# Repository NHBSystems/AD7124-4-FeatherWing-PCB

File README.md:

# AD7124-4 24bit Analog Sensor FeatherWing Design Files

This is a new Feather compatible board for reading precision analog sensors like load cells, thermocouples, and strain gauges. It uses the AD7124-4, a 4 channel, 24 bit, differential ADC (Can also be configured as 7 single ended channels). Like the [6 Channel 24 bit Featherwing](https://github.com/NHBSystems/6Ch-24bit-FeatherWing-PCB) this board is designed for lower power, monitoring type applications, however it can also be configured for significantly higher sampling rates than the AD7794. The board also includes a low pass anti-aliasing filter on the inputs, a 5th input pin for a shield wire connection, and software enabled excitation voltage without using an additional pin.

**Specifications**

- RMS noise down to 23 nV at 9.4 SPS
- Low power operation with 3 conversion power modes
- Power-down current of 5 μA maximum (AD7124 chip)
- Low noise, programmable gain instrumentation amplifier (1 to 128)
- Band gap reference with 10 ppm/°C drift typical
- Simultaneous 50 Hz/60 Hz rejection at 25 SPS
- Update rate: Up to 19200 sps (per datasheet for single channel)
- 4 differential analog inputs, (or 7 single ended)
- Independent configuration of each channel
- Low pass anti-aliasing filter on inputs
- 5 pin connections with excitation, ground, and shield for each channel
- Shield can be tied to chassis or to ground (trace jumper on bottom)
- On board 2.5v LDO controlled in software without needing additional pin
- Software enabled bias voltage on all channels (for reading thermocouples)

This board can be purchased assembled here: [24 bit Analog Sensor FeatherWing](https://www.tindie.com/products/24680/)

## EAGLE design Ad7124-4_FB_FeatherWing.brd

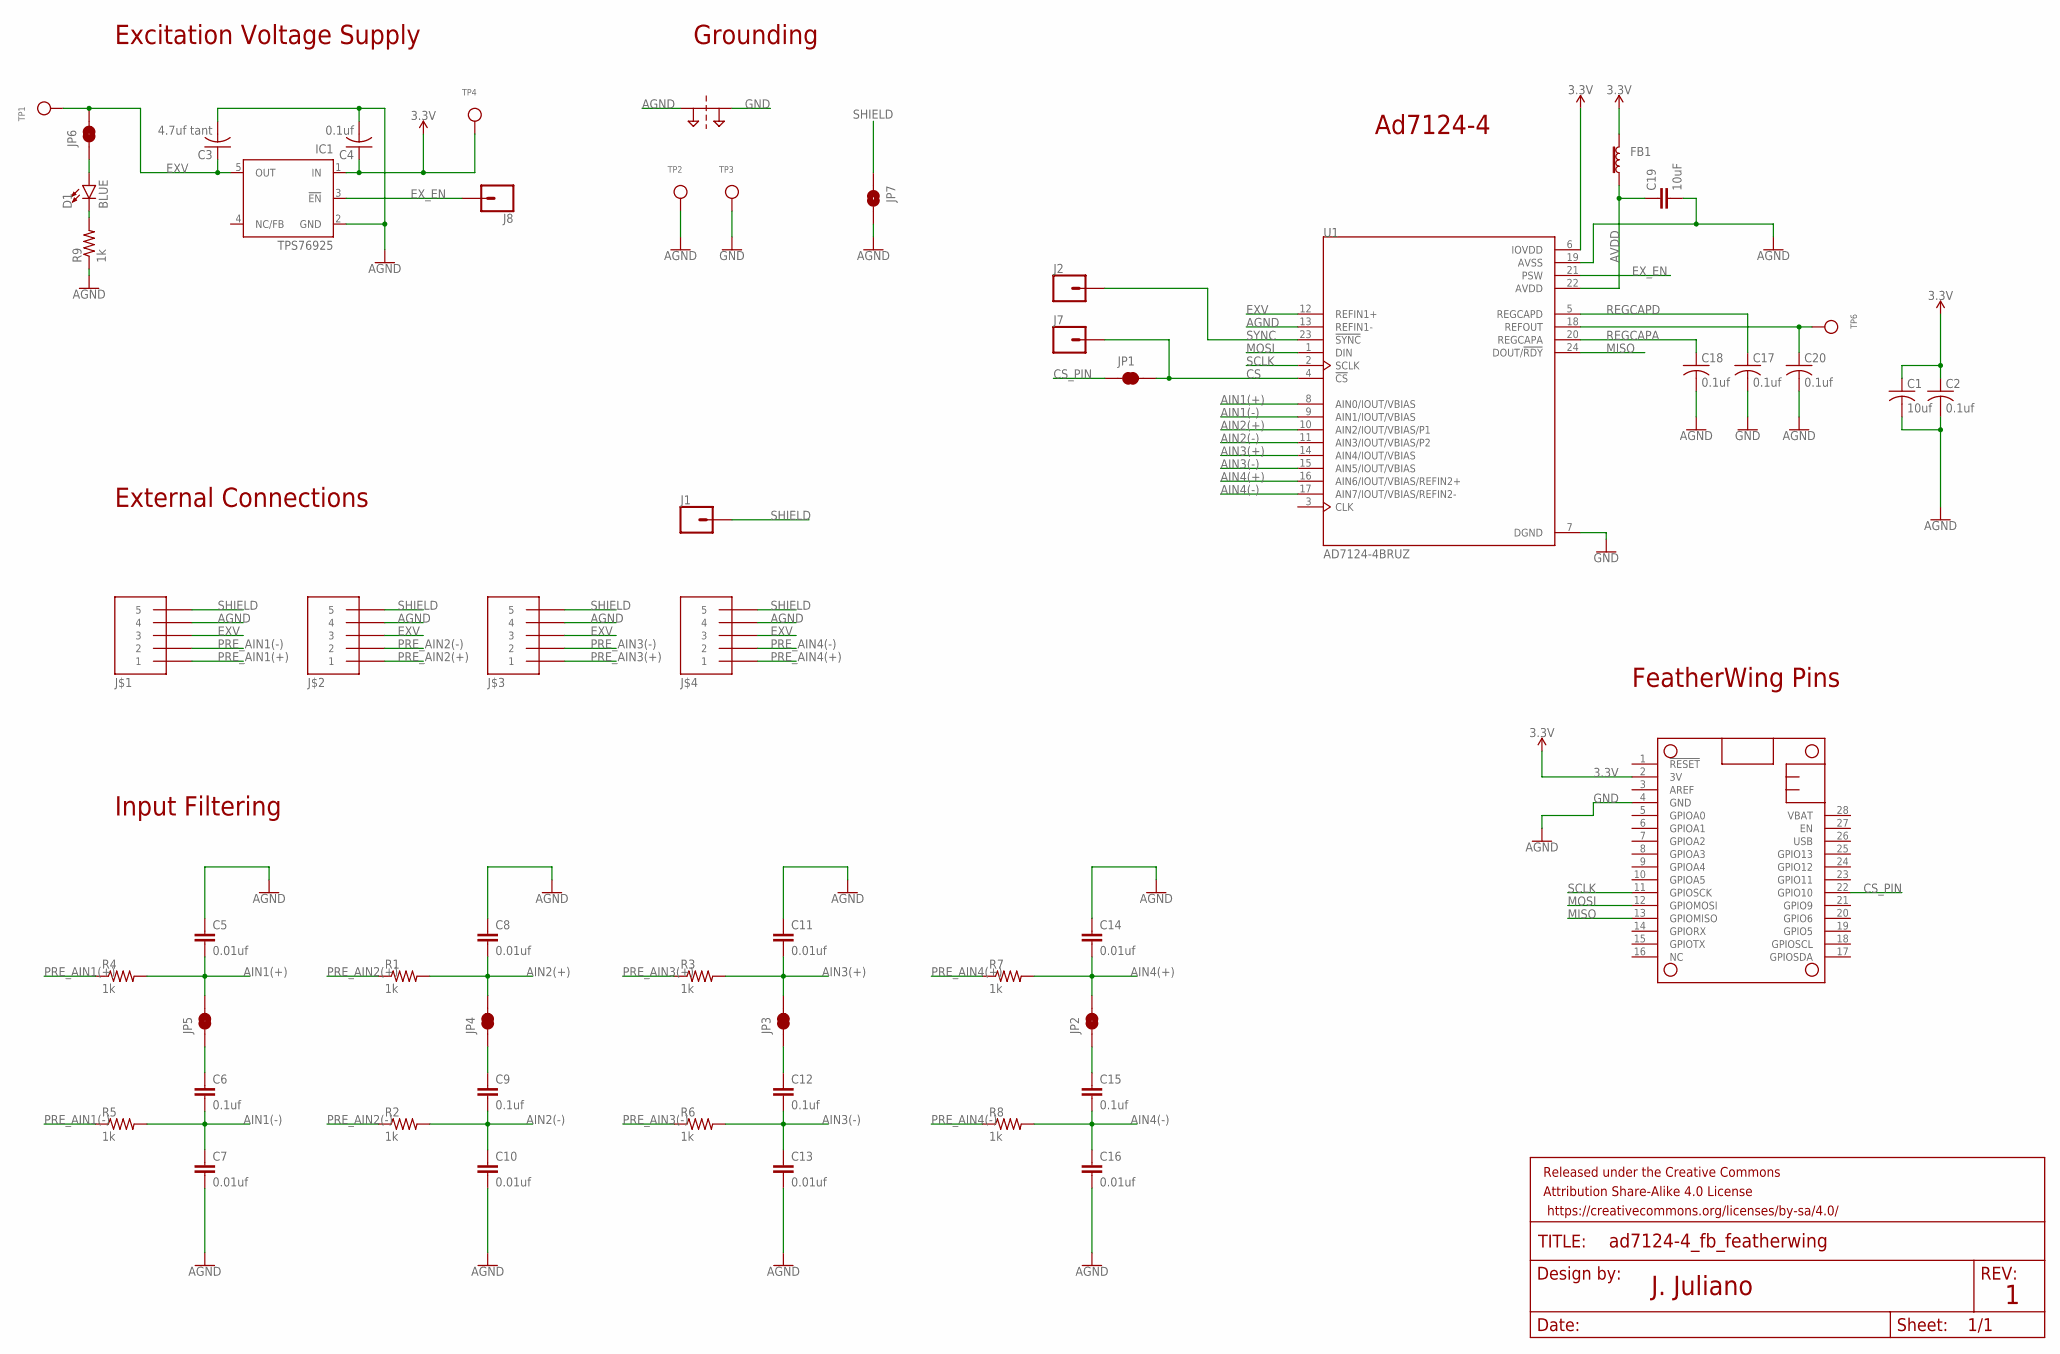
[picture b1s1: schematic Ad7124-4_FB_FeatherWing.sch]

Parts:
C1: 10uf; C0603
C2, C4, C6, C9, C12, C15, C17, C18, C20: 0.1uf; C0603
C3: 4.7uf tant; C0603
C5, C7, C8, C10, C11, C13, C14, C16: 0.01uf; C0603
C19: 10uF; 0603
D1: BLUE; LED-0603
FB1: FERRITE_BEAD-0603; 0603
FRAME2: FRAME-LETTER; CREATIVE_COMMONS
IC1: TPS76925; SOT23-DBV
J1, J2, J7, J8: CONN_01PTH_NO_SILK_YES_STOP; 1X01_NO_SILK
J$1, J$2, J$3, J$4: CON_PTSM_SOCKET-5-PTH-VERT
JP1, JP2, JP3, JP4, JP5, JP6: JUMPER-SMT_2_NC_TRACE_NO-SILK; SMT-JUMPER_2_NC_TRACE_NO-SILK
JP7: JUMPER-SMT_2_NO_NO-SILK; SMT-JUMPER_2_NO_NO-SILK
MS1: FEATHERWING_NODIM; FEATHERWING_DIM
R1, R2, R3, R4, R5, R6, R7, R8, R9: 1k; R0603
SUPPLY6: 2PT_GND_TIE
TP1, TP2, TP3, TP4, TP6: TESTPOINTROUND1MM; TESTPOINT_ROUND_1MM
U1: AD7124-4BRUZ; SOP65P640X120-24N

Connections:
3.3V: C1.1, C2.1, C4.1, FB1.2, IC1.1 (IN), MS1.2 (3V), TP4.P$1, U1.6 (IOVDD)
AGND: C5.1, C7.2, C8.1, C10.2, C11.1, C13.2, C14.1, C16.2, C18.2, C19.2, C20.2, J$1.P$4 (4), J$2.P$4 (4), J$3.P$4 (4), J$4.P$4 (4), JP7.2, R9.1, SUPPLY6.P$1, TP2.P$1, U1.13 (REFIN1-), U1.19 (AVSS)
AIN1(+): C5.2, JP5.2, R4.2, U1.8 (AIN0/IOUT/VBIAS)
AIN1(-): C6.2, C7.1, R5.2, U1.9 (AIN1/IOUT/VBIAS)
AIN2(+): C8.2, JP4.2, R1.2, U1.10 (AIN2/IOUT/VBIAS/P1)
AIN2(-): C9.2, C10.1, R2.2, U1.11 (AIN3/IOUT/VBIAS/P2)
AIN3(+): C11.2, JP3.2, R3.2, U1.14 (AIN4/IOUT/VBIAS)
AIN3(-): C12.2, C13.1, R6.2, U1.15 (AIN5/IOUT/VBIAS)
AIN4(+): C14.2, JP2.2, R7.2, U1.16 (AIN6/IOUT/VBIAS/REFIN2+)
AIN4(-): C15.2, C16.1, R8.2, U1.17 (AIN7/IOUT/VBIAS/REFIN2-)
AVDD: C19.1, FB1.1, U1.22 (AVDD)
CS: J7.1, JP1.2, U1.4 (!CS)
CS_PIN: JP1.1, MS1.22 (GPIO10)
EXV: C3.1, IC1.5 (OUT), J$1.P$3 (3), J$2.P$3 (3), J$3.P$3 (3), J$4.P$3 (3), JP6.2, TP1.P$1, U1.12 (REFIN1+)
EX_EN: IC1.3 (!EN), J8.1, U1.21 (PSW)
GND: C1.2, C2.2, C3.2, C4.2, C17.2, IC1.2 (GND), MS1.4 (GND), SUPPLY6.P$2, TP3.P$1, U1.7 (DGND)
MISO: MS1.13 (GPIOMISO), U1.24 (DOUT/!RDY)
MOSI: MS1.12 (GPIOMOSI), U1.1 (DIN)
unnamed: D1.A, JP6.1
unnamed: C15.1, JP2.1
unnamed: C12.1, JP3.1
unnamed: D1.C, R9.2
unnamed: C9.1, JP4.1
unnamed: C6.1, JP5.1
unnamed: C20.1, TP6.P$1, U1.18 (REFOUT)
PRE_AIN1(+): J$1.P$1 (1), R4.1
PRE_AIN1(-): J$1.P$2 (2), R5.1
PRE_AIN2(+): J$2.P$1 (1), R1.1
PRE_AIN2(-): J$2.P$2 (2), R2.1
PRE_AIN3(+): J$3.P$1 (1), R3.1
PRE_AIN3(-): J$3.P$2 (2), R6.1
PRE_AIN4(+): J$4.P$1 (1), R7.1
PRE_AIN4(-): J$4.P$2 (2), R8.1
REGCAPA: C18.1, U1.20 (REGCAPA)
REGCAPD: C17.1, U1.5 (REGCAPD)
SCLK: MS1.11 (GPIOSCK), U1.2 (SCLK)
SHIELD: J1.1, J$1.P$5 (5), J$2.P$5 (5), J$3.P$5 (5), J$4.P$5 (5), JP7.1
SYNC: J2.1, U1.23 (!SYNC)

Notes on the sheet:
Excitation Voltage Supply
FeatherWing Pins
Ad7124-4
External Connections
Input Filtering
J. Juliano
Grounding

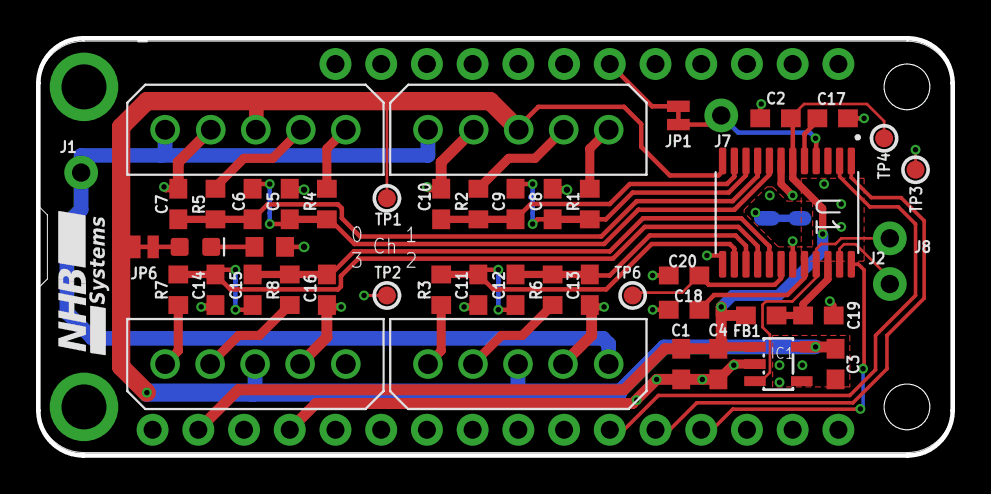
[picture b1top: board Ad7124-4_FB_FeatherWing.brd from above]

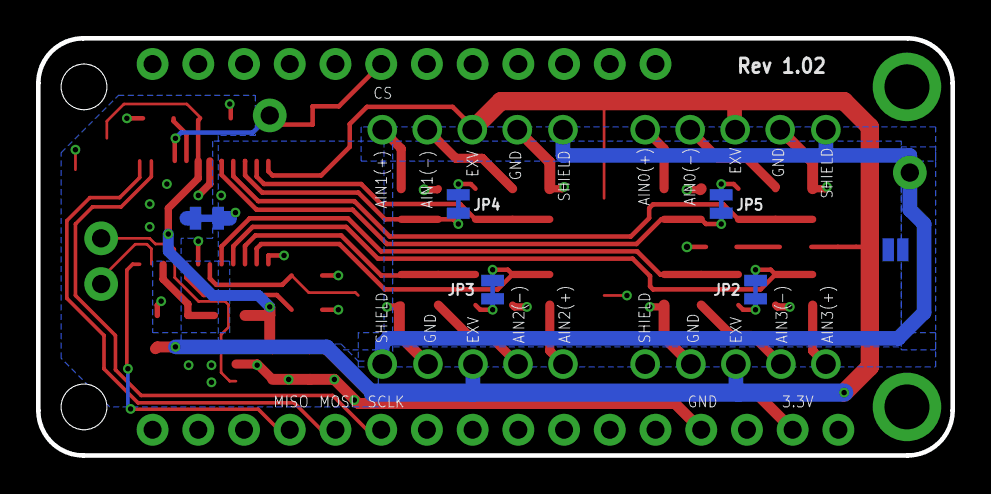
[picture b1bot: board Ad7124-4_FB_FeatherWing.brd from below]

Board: 2 copper layers, 50.8 x 23.2 mm, 57 parts (6 on the bottom side), 38 nets.

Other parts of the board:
U$5: NHB_COMPACT_LOGO_SMALL

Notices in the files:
parts and their libraries:
SparkFun-Connectors: Licensing: Creative Commons ShareAlike 4.0 International - https://creativecommons.org/licenses/by-sa/4.0
microbuilder: This work is placed in the public domain, and may be freely used for commercial and non-commercial work with the following conditions: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
